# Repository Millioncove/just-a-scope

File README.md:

# The simplest oscilloscope imaginable.
just-a-scope is a battery powered, ultra light, and tiny oscilloscope.

Often times when working on embedded projects, once GPIO has just been configured and you take the leap from programming into the real world, you cannot even get a blinky program running. Even if you are lucky enough to succeed in your LED-blinking, whatever you are moving onto next won't work. It is simply way more complicated than a single LED. 

At that point you wish you could "just see the electricity", but you cannot. You wish you had an oscilloscope, but all of the commercially available ones are extremely overkill and way out of budget. This is the problem just-a-scope tries to solve.

just-a-scope is really just an esp32 with some protection, scaling electronics and probes connected to the Analog-to-Digital converter. 9 times out of 10, that's all we'll ever need.

The plot is drawn in a web browser on a device connected over WIFI. At that point you already have the entire plot on your computer, and you can download a .csv file with all measurements made.

## Hardware
The microcontroller is an esp32s3, bought already soldered onto a SEEED Studio XIAO. This is a cheap and very small board which includes a USB-C connector as well as charging electronics for a lithium battery.

When buying one of these boards, you are likely to receive an antenna in the same package. This antenna is known to be unusable due to very poor signal, so a third party antenna must be used.

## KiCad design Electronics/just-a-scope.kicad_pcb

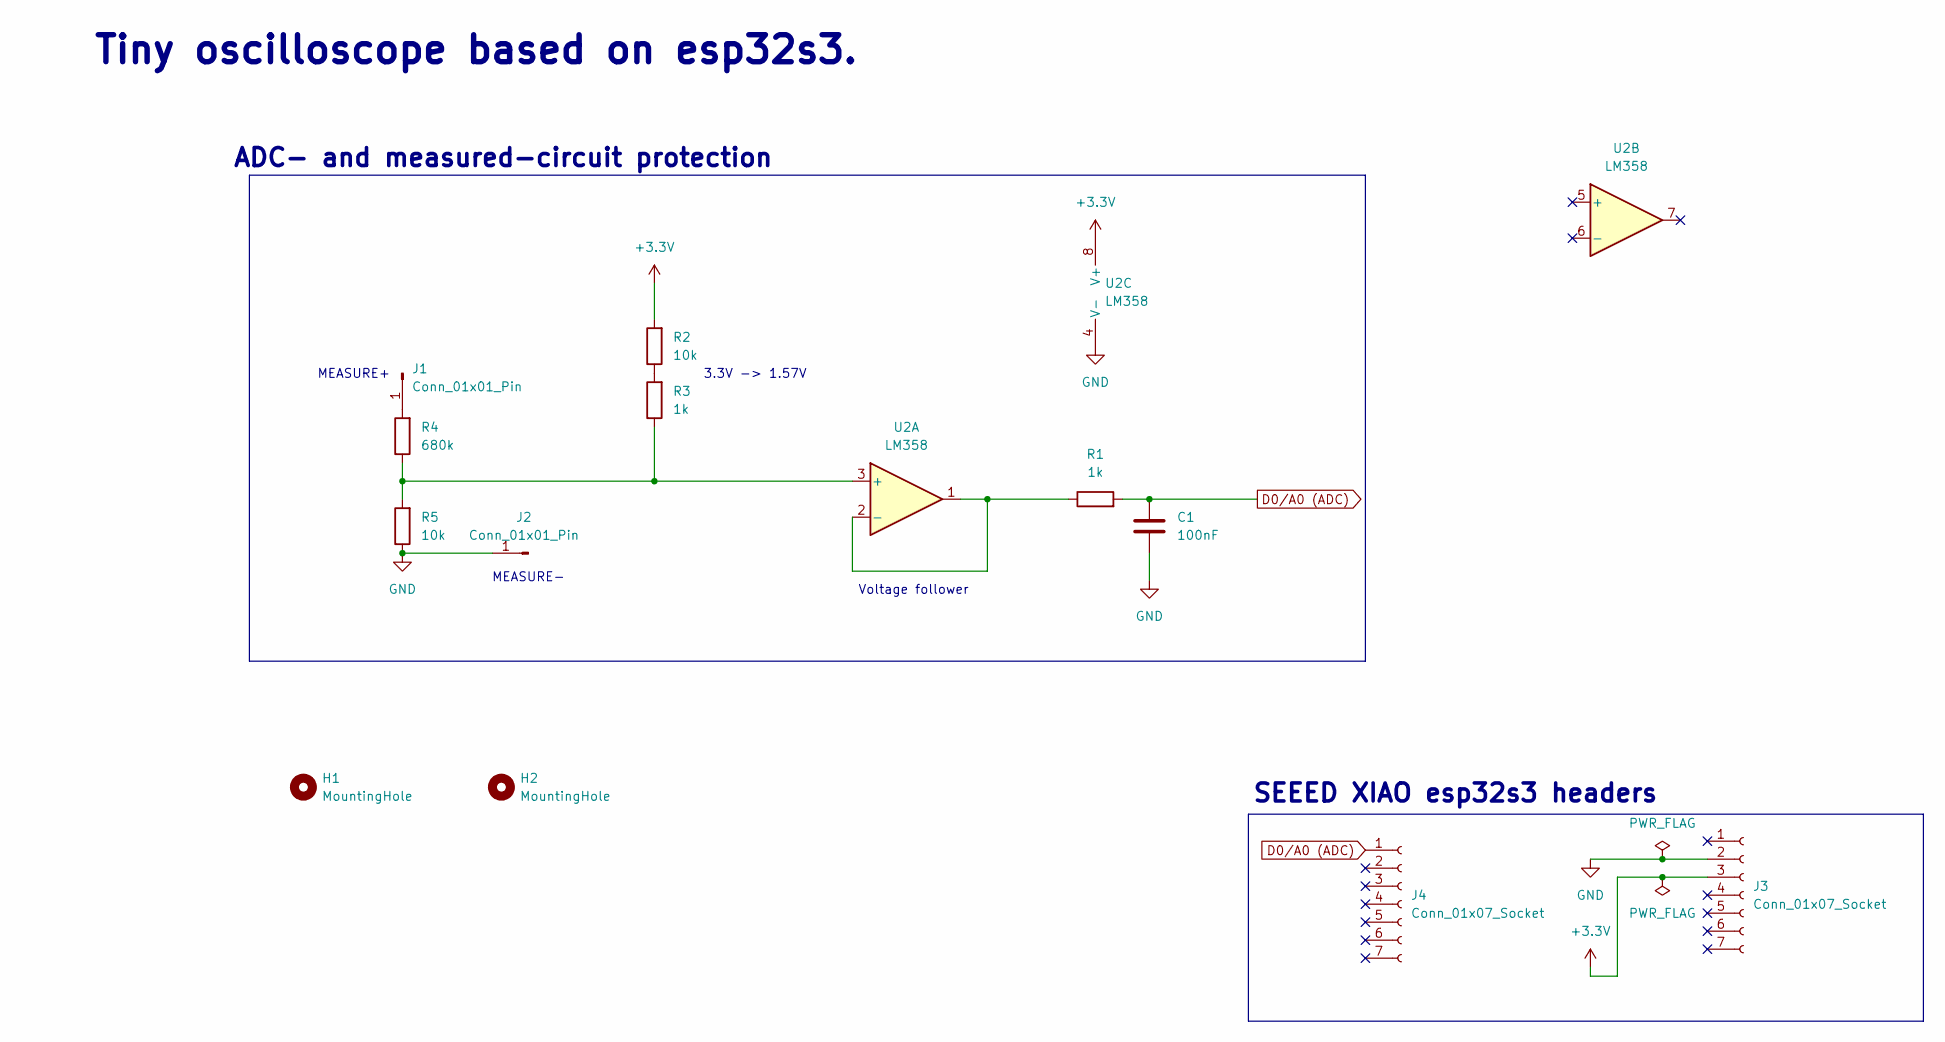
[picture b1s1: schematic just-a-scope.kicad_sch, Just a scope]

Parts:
C1: 100nF; C_0805_2012Metric
H1, H2: MountingHole; MountingHole_3.2mm_M3
J1, J2: Conn_01x01_Pin; SolderWirePad_1x01_SMD_5x10mm
J3, J4: Conn_01x07_Socket; PinSocket_1x07_P2.54mm_Vertical
R1, R3: 1k; R_0805_2012Metric
R2, R5: 10k; R_0805_2012Metric
R4: 680k; R_0805_2012Metric
U2: LM358; SOIC-8_3.9x4.9mm_P1.27mm

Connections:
+3.3V: J3.3, R2.2, U2.8 (V+)
D0/A0 (ADC): C1.1, J4.1, R1.2
GND: C1.2, J2.1, J3.2, R5.1, U2.4 (V-)
unnamed: J1.1, R4.2
unnamed: R2.1, R3.2
unnamed: R3.1, R4.1, R5.2, U2.3 (+)
unnamed: R1.1, U2.1, U2.2 (-)

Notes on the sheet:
3.3V -> 1.57V
Voltage follower
MEASURE+
MEASURE-
Tiny oscilloscope based on esp32s3.
ADC- and measured-circuit protection
SEEED XIAO esp32s3 headers

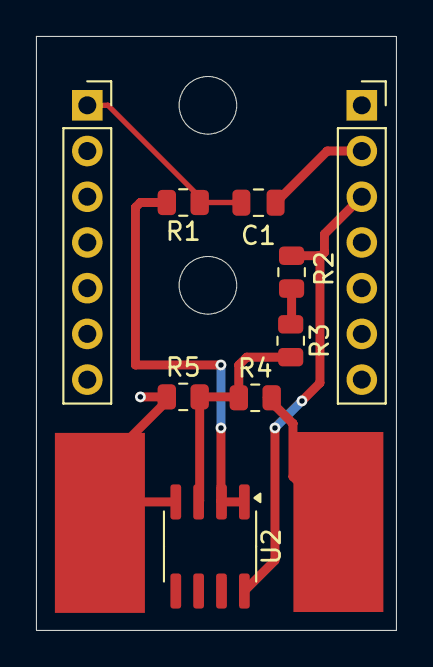
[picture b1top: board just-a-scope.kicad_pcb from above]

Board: 2 copper layers, 20.0 x 33.0 mm, 13 parts (0 on the bottom side), 7 nets.

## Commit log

2024-12-15 Before changing to esp-hal-dhcp-server
2024-12-16 TCP socket works! (barely)
2024-12-21 Http server is working! No dhcp tho.
2024-12-21 Web page draft.
2024-12-21 WebSocket handshake recognition.
2024-12-21 Unsynced initial commit. Whoops.
2024-12-22 Successfully establishes a WebSocket connection.
2024-12-22 WebSocket messages proof-of-concept.
2024-12-23 Better framework for sending WebSocket messages.
2024-12-24 Now works as a station and still creates an AP!
2024-12-25 Enabled formatting.
2024-12-25 Properly set up workspace.
2024-12-26 Multi core for measurements.
2024-12-28 Sending bigger WebSocket messages, and buffering of measurements.
2024-12-28 Optimization and cleaning.
2024-12-28 More optimizations.
2025-01-01 Now filters out redundant points! Cleaning needed...
2025-01-02 Cleaned and optimized.
2025-01-03 UX and CSV files.
2025-01-09 Now measures voltage.
2025-01-11 Electronics and pcb.
2025-01-11 Added calibration to ADC.
2025-01-11 Dependency maintenance.
2025-01-13 Adjustments for voltage from measurement circuit.
2025-01-13 Made configuration more standardized.
2025-01-14 Multisampling to reduce noise.
2025-01-14 More reasonable voltage range. (code only)
2025-01-15 Better number of digits on monitor.
2025-01-15 Fullscreen, fading buttons, UX.
2025-01-16 Adjustable measurement frequency in config.toml
2025-01-16 Automatic scrolling implemented
2025-01-19 Battery-less enclosure CAD.
2025-01-21 Poor mans profiler.
2025-02-08 Enclosure with battery.
2025-02-09 Better config, now called "Settings.toml".
2025-02-09 Readme!
2025-02-09 Small UX update.
2025-02-09 Bugfix: Only half of voltage measured.
